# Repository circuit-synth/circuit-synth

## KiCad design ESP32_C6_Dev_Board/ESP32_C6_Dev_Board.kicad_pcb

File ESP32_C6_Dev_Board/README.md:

# ESP32_C6_Dev_Board

A circuit-synth project converted from an existing KiCad design.

## 🚀 Quick Start

```bash
# Run the converted circuit
uv run python circuit-synth/main.py

# Test circuit-synth is working
uv run python -c "from circuit_synth import *; print('✅ Circuit-synth ready!')"
```

## 📁 Project Structure

```
ESP32_C6_Dev_Board/
├── circuit-synth/        # Circuit-synth Python files
│   └── main.py           # Main circuit (converted from KiCad)
├── *.kicad_pro          # Original KiCad project file
├── *.kicad_sch          # Original KiCad schematic  
├── *.kicad_pcb          # Original KiCad PCB (if present)
├── .claude/             # AI agents for Claude Code
│   ├── agents/          # Specialized circuit design agents
│   └── commands/        # Slash commands
├── README.md           # This file
└── CLAUDE.md           # Project-specific Claude guidance
```

## 🔄 Next Steps

1. **Review the generated code** in `circuit-synth/main.py`
2. **Update component symbols and footprints** as needed
3. **Verify net connections** match your original design
4. **Test the circuit generation** with `uv run python circuit-synth/main.py`
5. **Use Claude Code agents** for AI-assisted improvements

## 🤖 AI-Powered Design

This project includes specialized AI agents:
- **circuit-synth**: Circuit code generation and KiCad integration
- **simulation-expert**: SPICE simulation and validation  
- **jlc-parts-finder**: JLCPCB component sourcing
- **orchestrator**: Master coordinator for complex projects

Use natural language to improve your design:
```
👤 "Optimize this power supply for better efficiency"
👤 "Add protection circuits to prevent overcurrent"  
👤 "Find alternative components available on JLCPCB"
```

## 📖 Documentation

- Circuit-Synth: https://circuit-synth.readthedocs.io
- KiCad: https://docs.kicad.org

**Happy circuit designing!** 🎛️

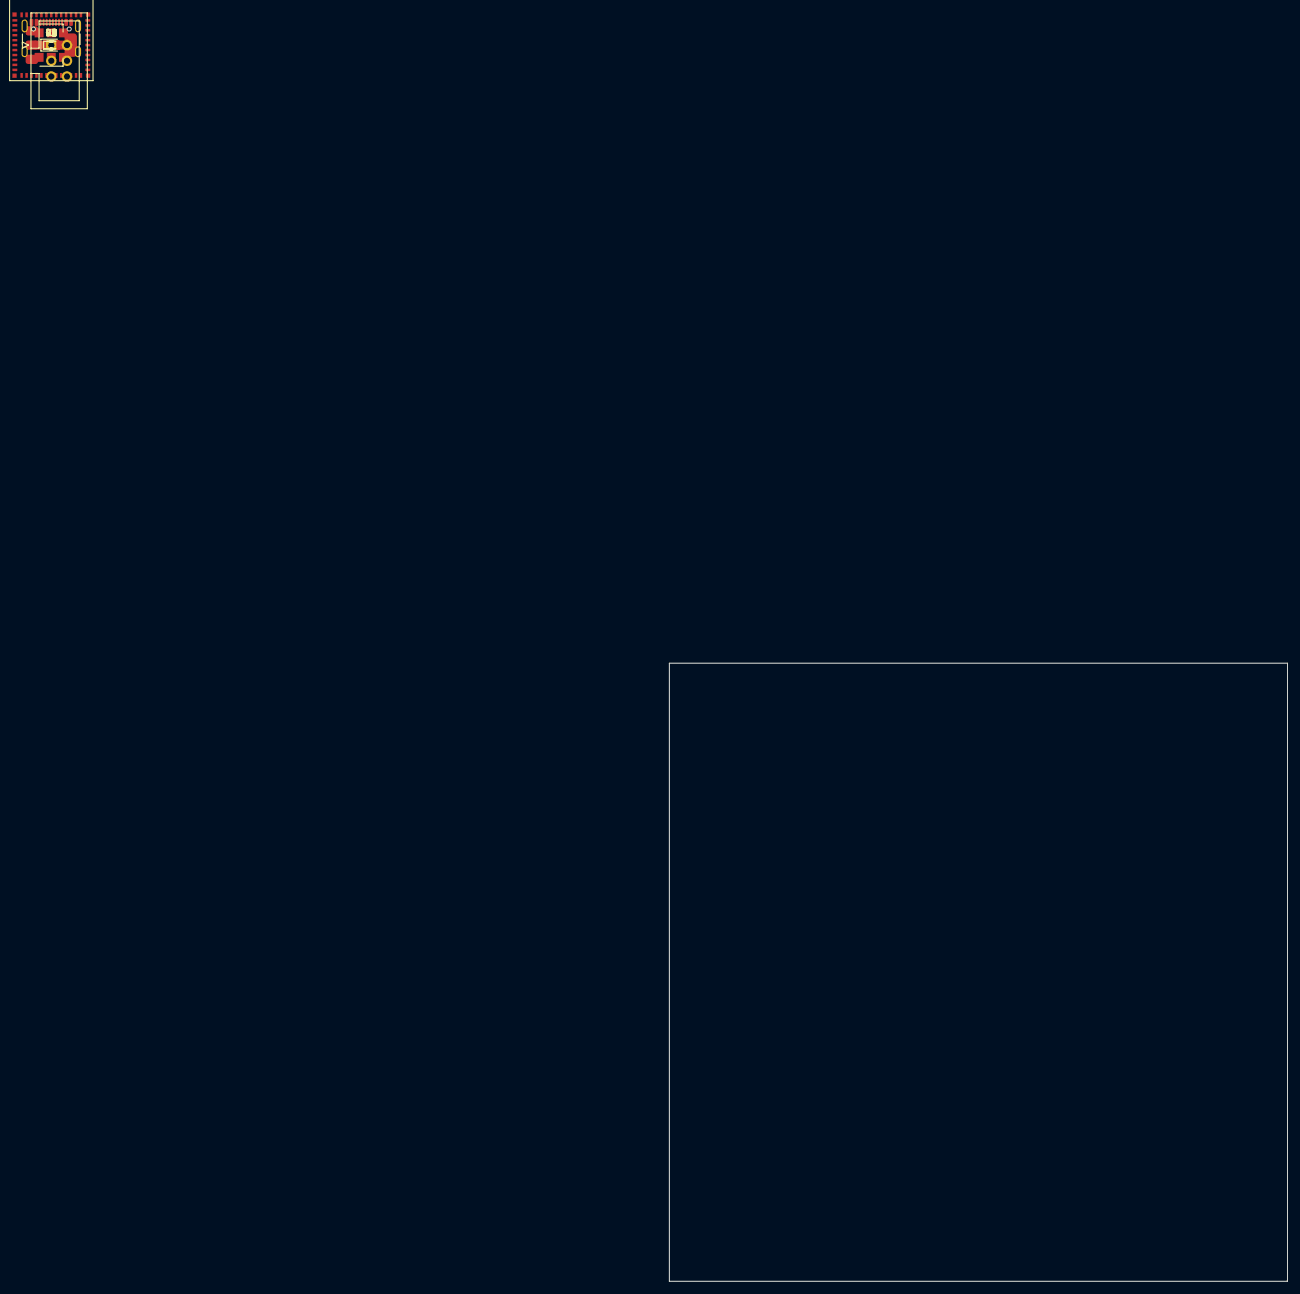
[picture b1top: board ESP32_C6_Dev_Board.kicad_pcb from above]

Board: 2 copper layers, 100.0 x 100.0 mm, 16 parts (0 on the bottom side), 15 nets, no tracks yet.

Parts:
C1, C2: 10uF; C_0805_2012Metric
C3: 22uF; C_0805_2012Metric
C4: 100nF; C_0603_1608Metric
D1, D2: D_SOD-523
D3: LED_0805_2012Metric
J1: USB_C_Receptacle_GCT_USB4105-xx-A_16P_TopMnt_Horizontal
J2: IDC-Header_2x03_P2.54mm_Vertical
R1, R2: 5.1k; R_0603_1608Metric
R3: 330; R_0805_2012Metric
R4, R5: 22; R_0603_1608Metric
U1: SOT-223-3_TabPin2
U2: ESP32-C6-MINI-1

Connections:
DEBUG_EN: J2.1, U2.8
DEBUG_IO0: J2.6, U2.12
DEBUG_RX: J2.5, U2.30
DEBUG_TX: J2.3, U2.31
GND: C1.2, C2.2, C3.2, C4.2, D1.2, D2.2, J1.A1, J1.A12, J1.B1, J1.B12, J1.S1, J2.4, R1.2, R2.2, U1.1, U2.1, U2.2, U2.11, U2.14, U2.36, U2.37, U2.38, U2.39, U2.40, U2.41, U2.42, U2.43, U2.44, U2.45, U2.46, U2.47, U2.48, U2.49, U2.50, U2.51, U2.52, U2.53
LED_CONTROL: D3.1, U2.22
unnamed: J1.A5, R1.1
unnamed: J1.B5, R2.1
unnamed: D3.2, R3.2
USB_DM: D2.1, J1.A7, J1.B7, R5.1
USB_DM_MCU: R5.2, U2.25
USB_DP: D1.1, J1.A6, J1.B6, R4.1
USB_DP_MCU: R4.2, U2.24
VBUS: C1.1, C2.1, J1.A4, J1.A9, J1.B4, J1.B9, U1.3
VCC_3V3: C3.1, C4.1, J2.2, R3.1, U1.2, U2.3

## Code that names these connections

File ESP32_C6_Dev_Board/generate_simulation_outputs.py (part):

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
        if bit == 1:
            usb_dp[mask] = 3.3
            usb_dm[mask] = 0
        else:
            usb_dp[mask] = 0
            usb_dm[mask] = 3.3

    # Add rise/fall time effects (4ns)
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        mask_low = (time_us >= mid) & (time_us < end)

        led_control[mask_high] = 3.3
        led_control[mask_low] = 0

    # LED cathode voltage (after 1k resistor)
    # When GPIO high: V_cathode = 3.3V - (I_LED * R) = 3.3 - (0.0013 * 1000) = 2.0V
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
    # LED current (mA)
    led_current = np.zeros_like(time_us)
    led_current[led_control > 1.5] = (3.3 - 2.0) / 1.0  # (V_GPIO - V_LED) / R in mA

    # 1. CSV Output
    csv_path = output_dir / "led_pwm_response.csv"
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        "LED Driver - PWM Control (100kHz, 50% Duty)",
        time_us,
        {
            "GPIO Control": led_control,
            "LED Voltage": led_cathode,
            "LED Current (mA)": led_current,
        },
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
